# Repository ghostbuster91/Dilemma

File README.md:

This is a modified version of Dilemma keyboard 3x6_3 with more aggerssive pinky stagger.

Head over [here](./dilemma/build_guide.md) for a build guide.

QMK firmaware: https://github.com/ghostbuster91/qmk_firmware/tree/bkb-master/keyboards/bastardkb/dilemma/3x6_3

<div align="center">

</div>

---

The Dilemma is a vertical stagger low-profile keyboard with mods.

## Table of contents

- [Features](#features)
- [Versions](#versions)
- [Wireless abilities](#wireless-abilities)
- [BOM](#bom)
  - [DIY version](#diy-version)
  - [Assembled version](#assembled-version)
  - [Trackpad mod](#trackpad-mod)
  - [Cases](#cases)
- [Community mods](#community-mods)
- [Build guide](#build-guide)
- [Forks](#forks)
- [Support me on patreon](#support-me-on-patreon)
- [Others / in progress](#others--in-progress)

---

## Features

- Heavy pinky stagger
- MX and choc compatible
- Reversible PCB
- Elite-pi / Splinky / Nice!Nano compatible
- Tenting puck footprint

## Versions

There are 2 versions of the dilemma, in 2 folders:

- `dilemma`, for DIY that requires an additional MCU (eg. kb2040)
- `dilemma_assembled`, for PCB assembly

The Dilemma is **made for rp2040**, so if you go with the DIY version you should source your MCU board accordingly.

## Wireless abilities

ZMK does not support input devices at the moment, and QMK does not support BLE.

However, as this is meant to be a portable keyboard, some ground work has been laid with the DIY version:

- pinout compatible with nice!nano
- 2 battery connectors footprints: JST, and THT
- on / off button footprint

At this time, the assembled version does not support wireless.

## BOM

The PCB can work on standalone.

Depending on which version you go with, you will need to source different items.

On top of the basic build, you can add a range of options, which require additional components:

- 3d printed case
- mods (eg. trackpad)

Both versions of the Dilemma require:

| Part name       | Amount | Link / source |
| --------------- | ------ | ------------- |
| Audio jack      | 2      |               |
| Button, 4x4x1.5 | 2      |               |

### DIY version

On top of the parts mentioned above, you will need:

| Part name               | Amount | Link / source               |
| ----------------------- | ------ | --------------------------- |
| SOD123 Diodes           | 34     | Farnell, Mouser, Aliexpress |
| Dilemma PCB, DIY, 1.2mm | 2      | See Release section         |
| RP2040 MCU board        | 2      | KB2040, elite-pi...         |
| Header pins             | 2\*12  |                             |

Please note, **the Dilemma is compatible only with rp2040 boards !**

The release section contains the latest gerbers.

Order in 1.2mm thickness.

### Assembled version

On top of the parts mentioned above, you will need:

| Part name                     | Amount | Link / source       |
| ----------------------------- | ------ | ------------------- |
| Dilemma PCB, assembled, 1.2mm | 2      | See Release section |

The release section contains the latest gerbers with BOM and POS files.

Order in 1.2mm thickness.

### Trackpad mod

This is the first mod made for the keyboard - so it can function as a standalone input device.

It uses I2C on the DIY version, and SPI on the assembled version.

The DIY version requires removing 2 resistors from the trackpad (see build guide).

When installing the trackpad mod, you will need:

| Part name           | Amount | Link / source           |
| ------------------- | ------ | ----------------------- |
| M3 screw, torx, 6mm | 4      | Conrad                  |
| M3x5x5 screw insert | 4      | Aliexpress              |
| Cirque trackpad\*   | 1      | Mouser                  |
| 3d printed parts\*  |        | See `mechanical` folder |

\*You can use either the 35mm (TM035035-2024-003) or 40mm (TM040040-2024-303).
Print the appropriate parts from the `mechanical` folder.

If building the PCBA version, you will also need:

| Part name                                                     | Amount | Link / source |
| ------------------------------------------------------------- | ------ | ------------- |
| 12-position FPC cable, 0.5mm pitch, same side contacts, 100mm | 1      | Farnell       |

If building the DIY version, you will also need:

| Part name               | Amount | Link / source |
| ----------------------- | ------ | ------------- |
| SOD123 Resistor, 5kOhms | 2      |               |
| Cables                  |        |               |

### Cases

There are a range of cases available. See details in the `mechanical/cases` folder.

## Community mods

There are a range of community mods available (hex plates, covers...).

You can find more information in the readme in the `mechanical/community mods` folder.

## Build guide

https://docs.bastardkb.com/hc/en-us/sections/6848232395410-Dilemma

## Forks

- [3x6 version](https://github.com/bstiq/Dilemma_3x6/)
- [3x5 + 3 version](https://github.com/dixls/Dilemma-3mod)

## Support me on Patreon

If you like the keyboard, please consider helping me with Patreon: https://www.patreon.com/bastardkb

I post regular updates and hindsight on my work. I work full time on keyboard innovation, and this helps a lot !

## Others / in progress

The PCB has available connectors for:

- oled

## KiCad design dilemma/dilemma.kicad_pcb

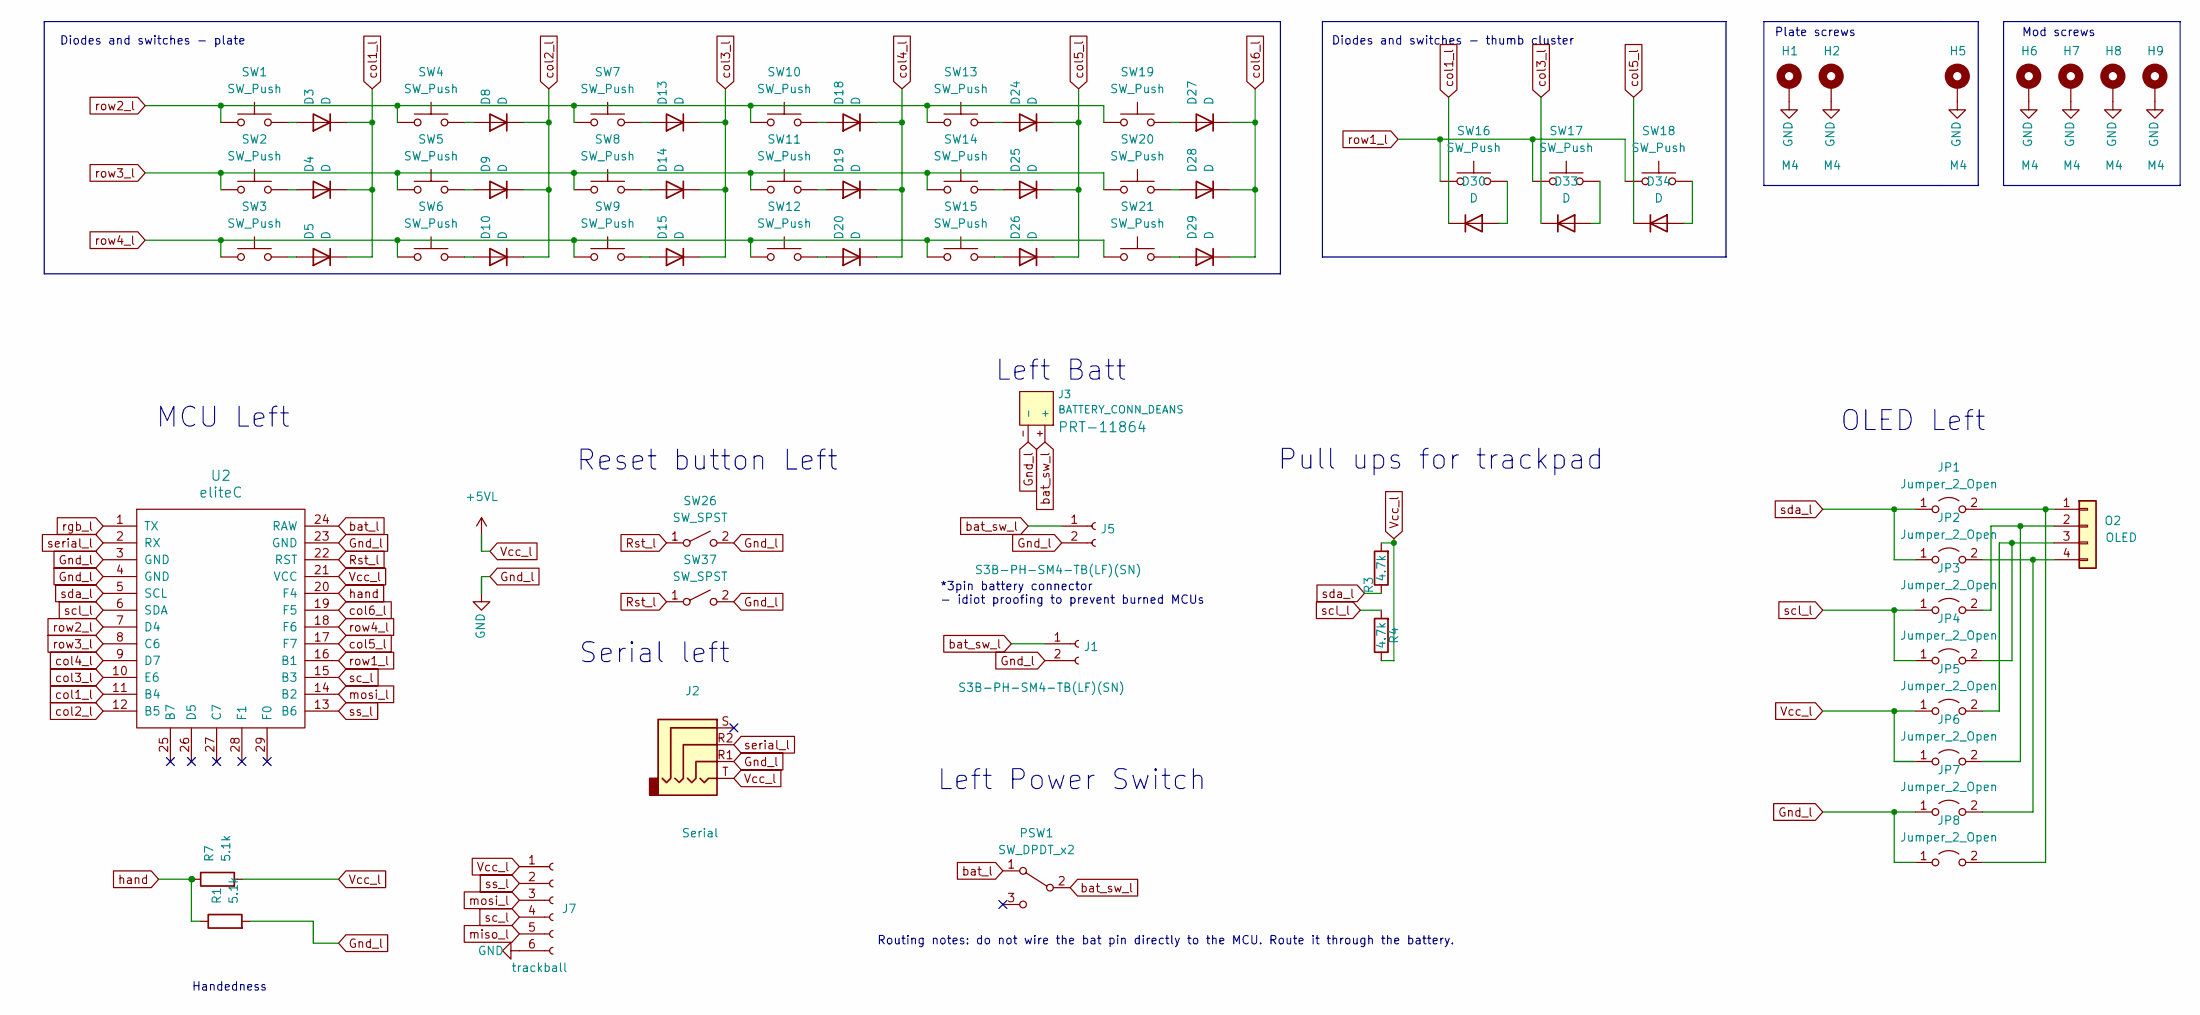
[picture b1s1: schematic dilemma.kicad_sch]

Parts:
D3, D4, D5, D8, D9, D10, D13, D14, D15, D18, D19, D20, D24, D25, D26, D27, D28, D29, D30, D33, D34: D; D_1206_handsolder_reversible
H1, H2, H5, H6, H7, H8, H9: M4; MountingHole_3mm_Pad_thin
J1, J5: S3B-PH-SM4-TB(LF)(SN); JST_SH_BM02B-SRSS-TB_1x02-1MP_P1.00mm_Vertical; LCSC C265101
J2: Serial; Jack_3.5mm_PJ320E_Horizontal_reversible
J3: BATTERY_CONN_DEANS; battery_connector_THT
J7: trackball; 6_PinHeader
JP1, JP2, JP3, JP4, JP5, JP6, JP7, JP8: Jumper_2_Open; SolderJumper-2_P1.3mm_Open_RoundedPad1.0x1.5mm
O2: OLED; PinHeader_1x04_P2.54mm_Vertical
PSW1: SW_DPDT_x2; Switch_MSK-12C01-07; LCSC C431540
R1, R7: 5.1k; R_1206_handsolder; JLCPCB BOM 1
R3, R4: 4.7k; R_1206_handsolder_reversible; LCSC C269746
SW1, SW2, SW3, SW4, SW5, SW6, SW7, SW8, SW9, SW10, SW11, SW12, SW13, SW14, SW15, SW16, SW17, SW18, SW19, SW20, SW21: SW_Push; SW_MX_choc
SW26, SW37: SW_SPST; SW_Push_1P1T_NO_6x6mm_H9.5mm
U2: eliteC; pro-micro

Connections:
Gnd_l: H1.1, H2.1, H5.1, H6.1, H7.1, H8.1, H9.1, J1.2, J2.R1, J3.-, J5.2, J7.6, JP7.1 (A), JP8.1 (A), R1.2, SW26.2 (B), SW37.2 (B), U2.3 (GND), U2.4 (GND), U2.23 (GND); also elsewhere on the board
unnamed: D3.2 (A), SW1.2
unnamed: D4.2 (A), SW2.2
unnamed: D5.2 (A), SW3.2
unnamed: D8.2 (A), SW4.2
unnamed: D9.2 (A), SW5.2
unnamed: D10.2 (A), SW6.2
unnamed: D13.2 (A), SW7.2
unnamed: D14.2 (A), SW8.2
unnamed: D15.2 (A), SW9.2
unnamed: D18.2 (A), SW10.2
unnamed: D19.2 (A), SW11.2
unnamed: D20.2 (A), SW12.2
unnamed: D24.2 (A), SW13.2
unnamed: D25.2 (A), SW14.2
unnamed: D26.2 (A), SW15.2
unnamed: D30.2 (A), SW16.2
unnamed: D33.2 (A), SW17.2
unnamed: D34.2 (A), SW18.2
unnamed: JP1.2 (B), JP8.2 (B), O2.1
unnamed: JP2.2 (B), JP7.2 (B), O2.4
unnamed: JP3.2 (B), JP6.2 (B), O2.2
unnamed: JP4.2 (B), JP5.2 (B), O2.3
unnamed: D27.2 (A), SW19.2
unnamed: D28.2 (A), SW20.2
unnamed: D29.2 (A), SW21.2
Rst_l: SW26.1 (A), SW37.1 (A), U2.22 (RST)
Vcc_l: J2.T, J7.1, JP5.1 (A), JP6.1 (A), R3.2, R4.1, R7.2, U2.21 (VCC)
bat_l: PSW1.1 (A), U2.24 (RAW)
bat_sw_l: J1.1, J3.+, J5.1, PSW1.2 (B)
col1_l: D3.1 (K), D4.1 (K), D5.1 (K), D30.1 (K), U2.11 (B4)
col2_l: D8.1 (K), D9.1 (K), D10.1 (K), U2.12 (B5)
col3_l: D13.1 (K), D14.1 (K), D15.1 (K), D33.1 (K), U2.10 (E6)
col4_l: D18.1 (K), D19.1 (K), D20.1 (K), U2.9 (D7)
col5_l: D24.1 (K), D25.1 (K), D26.1 (K), D34.1 (K), U2.17 (F7)
col6_l: D27.1 (K), D28.1 (K), D29.1 (K), U2.19 (F5)
hand: R1.1, R7.1, U2.20 (F4)
mosi_l: J7.3, U2.14 (B2)
rgb_l: U2.1 (TX)
row1_l: SW16.1, SW17.1, SW18.1, U2.16 (B1)
row2_l: SW1.1, SW4.1, SW7.1, SW10.1, SW13.1, SW19.1, U2.7 (D4)
row3_l: SW2.1, SW5.1, SW8.1, SW11.1, SW14.1, SW20.1, U2.8 (C6)
row4_l: SW3.1, SW6.1, SW9.1, SW12.1, SW15.1, SW21.1, U2.18 (F6)
sc_l: J7.4, U2.15 (B3)
scl_l: JP3.1 (A), JP4.1 (A), R4.2, U2.6 (SDA)
sda_l: JP1.1 (A), JP2.1 (A), R3.1, U2.5 (SCL)
serial_l: J2.R2, U2.2 (RX)
ss_l: J7.2, U2.13 (B6)

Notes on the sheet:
MCU Left
Left Batt
Handedness
Plate screws
Routing notes: do not wire the bat pin directly to the MCU. Route it through the battery.
Serial left
Diodes and switches - plate
Reset button Left
Pull ups for trackpad
Mod screws
Left Power Switch
OLED Left
Diodes and switches - thumb cluster
*3pin battery connector - idiot proofing to prevent burned MCUs

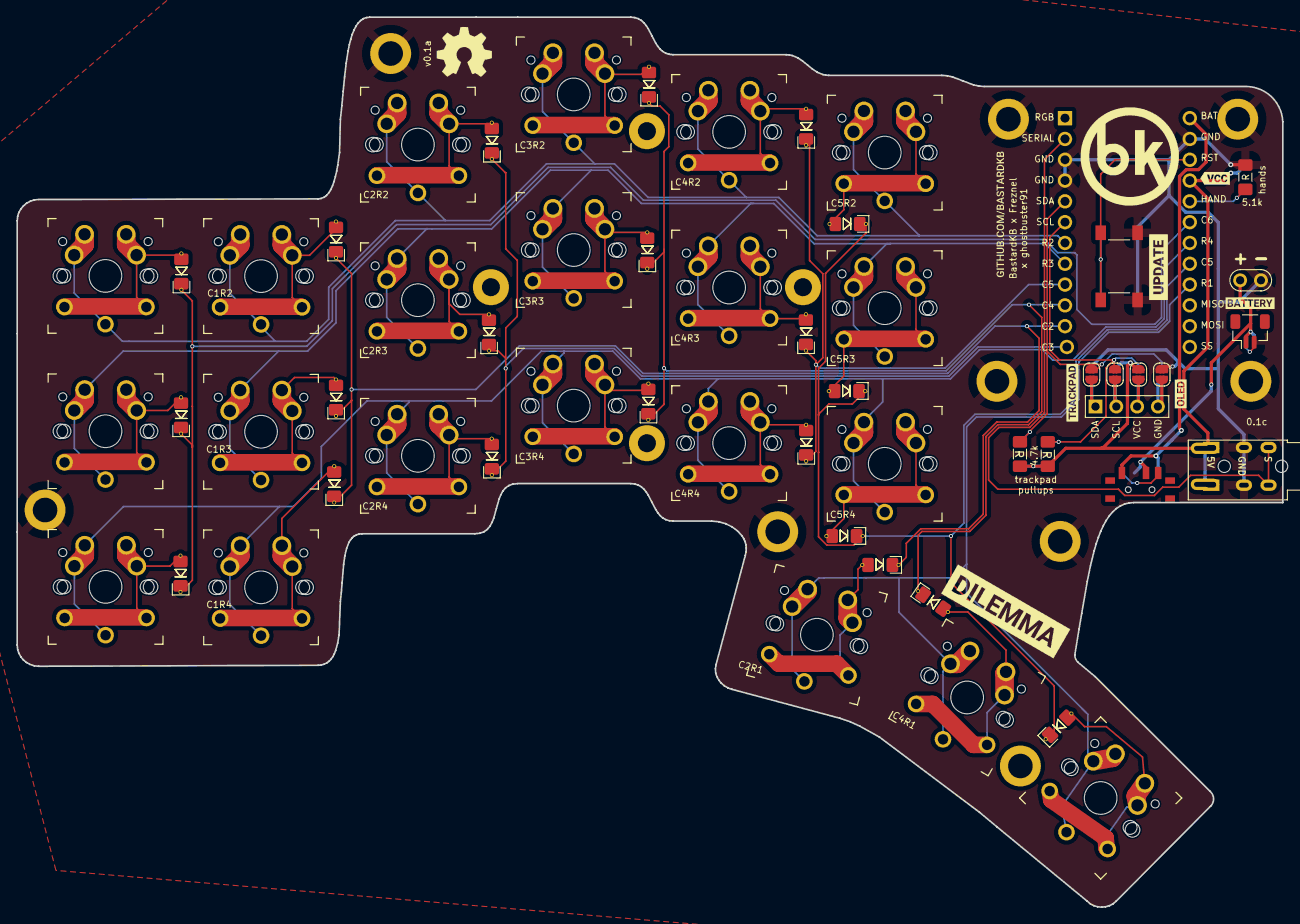
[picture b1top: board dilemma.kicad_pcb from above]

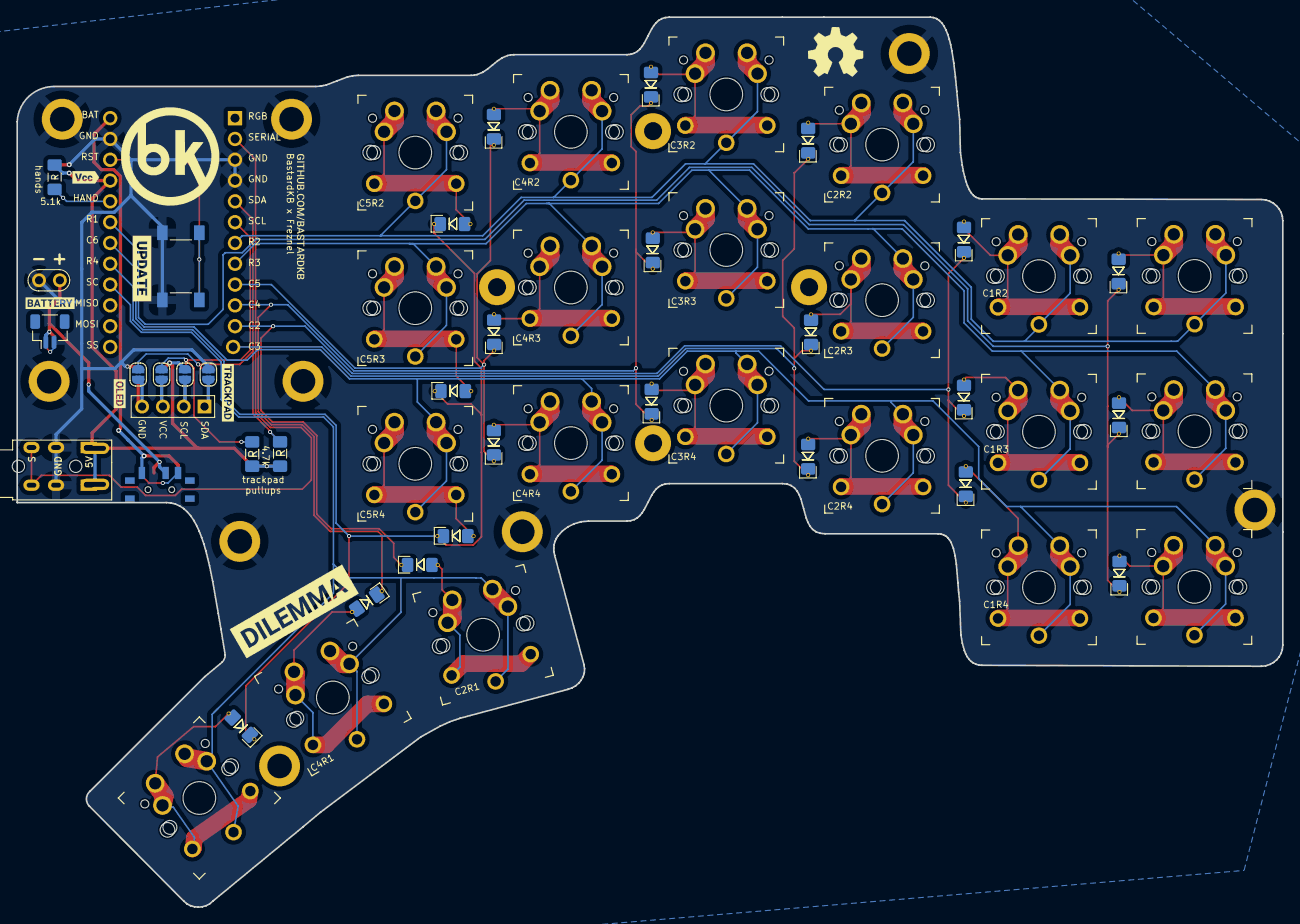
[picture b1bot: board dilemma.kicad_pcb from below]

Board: 2 copper layers, 154.5 x 108.7 mm, 85 parts (15 on the bottom side), 44 nets.

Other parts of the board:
H4: M4; MountingHole_3mm_Pad_thin
kibuzzard-61F01A92, kibuzzard-61F01A92#2: G***; kibuzzard-61F01A92
kibuzzard-61F01C84, kibuzzard-61F01C84#2: G***; kibuzzard-61F01C84
kibuzzard-628D3AA1: G***; kibuzzard-628D3AA1
kibuzzard-628D396A: G***; kibuzzard-628D396A
kibuzzard-628DFB5F, kibuzzard-628DFB5F#2: G***; kibuzzard-628DFB5F
kibuzzard-628DFB48, kibuzzard-628DFB48#2: G***; kibuzzard-628DFB48
kibuzzard-628DFB95, kibuzzard-628DFB95#2: G***; kibuzzard-628DFB95
kibuzzard-628E0199, kibuzzard-628E0199#2: G***; kibuzzard-628E0199

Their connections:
Gnd_l: H4.1; also elsewhere on the board

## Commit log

2023-03-01 Add keyboard-libraries submodule
2023-03-01 Add thumb key
2023-03-02 Create place for col6
2023-03-02 Add 6th column
2023-03-03 Fix drc errors
2023-03-03 Remove H4 hole
2023-03-08 Revert "Remove H4 hole"
    This reverts commit eafe3389c8530ed03ec8ad130b3a2f53ccdd09a2.
2023-03-08 Move mounting hole to the left
2023-03-08 Update slik screen layer
2023-03-08 Extend outline
2023-03-12 Add modified case for tenting_puck
2023-03-27 Add build guide
2023-04-14 Add link to qmk firmware
2023-04-14 Update case

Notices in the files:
README.md:
License: CERN OHL V2
